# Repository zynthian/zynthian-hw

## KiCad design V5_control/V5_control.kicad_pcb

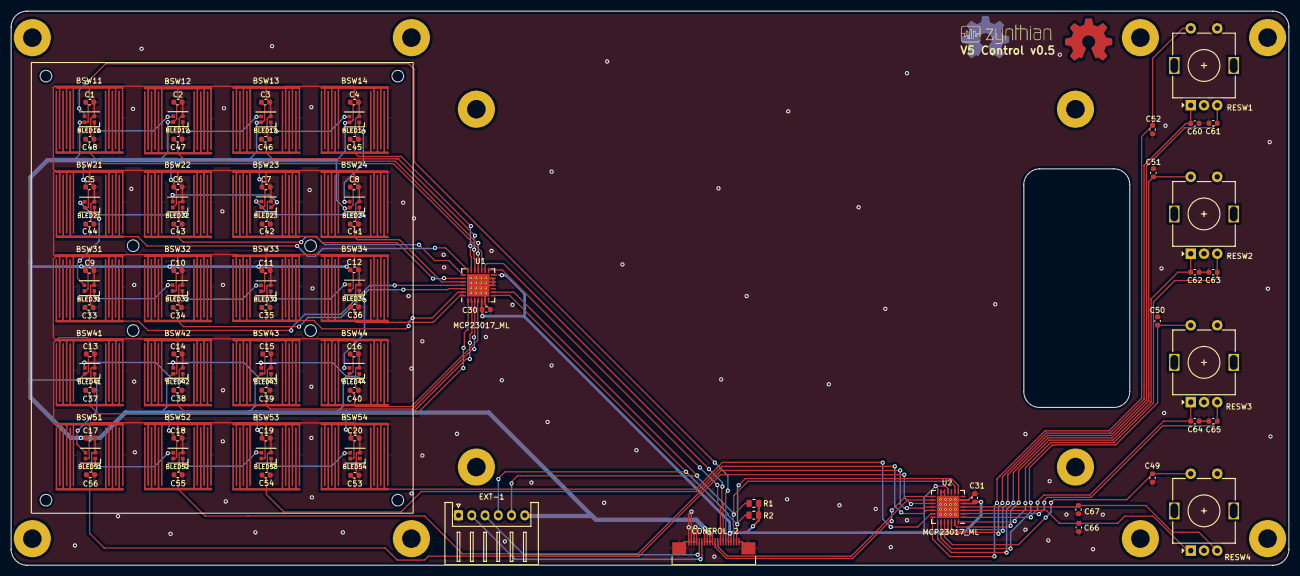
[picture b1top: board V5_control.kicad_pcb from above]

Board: 2 copper layers, 241.0 x 104.5 mm, 104 parts (0 on the bottom side), 63 nets.

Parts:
BLED11, BLED12, BLED13, BLED14, BLED21, BLED22, BLED23, BLED24, BLED31, BLED32, BLED33, BLED34, BLED41, BLED42, BLED43, BLED44, BLED51, BLED52, BLED53, BLED54: WS2812B; LED_WS2812-2020_2.2x2.0mm
BSW11, BSW12, BSW13, BSW14, BSW21, BSW22, BSW23, BSW24, BSW31, BSW32, BSW33, BSW34, BSW41, BSW42, BSW43, BSW44, BSW51, BSW52, BSW53, BSW54: SW_Push; V5-KeyPad_LED
C1, C2, C3, C4, C5, C6, C7, C8, C9, C10, C11, C12, C13, C14, C15, C16, C17, C18, C19, C20, C30, C31: 1uf; C_0603_1608Metric
C33, C34, C35, C36, C37, C38, C39, C40, C41, C42, C43, C44, C45, C46, C47, C48, C49, C50, C51, C52, C53, C54, C55, C56: 47nf16v; C_0603_1608Metric
C60, C61, C62, C63, C64, C65, C66, C67: 10nf16v; C_0603_1608Metric
CONTROL-2: Conn_01x22; SFV20R-4STE1LF_thinpads
EXT-1: Conn_01x06_Male; JST_XH_S6B-XH-A_1x06_P2.50mm_Horizontal
R1, R2: 10K; R_0805_2012Metric
RESW1, RESW2, RESW3, RESW4: Rotary_Encoder_Switch; RotaryEncoder_Alps_EC11E-Switch_Vertical_H20mm
U1, U2: MCP23017_ML; QFN-28-1EP_6x6mm_P0.65mm_EP4.25x4.25mm_ThermalVias

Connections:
3.3v: C30.1, C31.1, CONTROL-2.16, CONTROL-2.17, R1.1, R2.1, U1.5 (VDD), U1.14 (~RESET), U2.5 (VDD), U2.11 (A0), U2.14 (~RESET)
5v: BLED11.4 (VDD), BLED12.4 (VDD), BLED13.4 (VDD), BLED14.4 (VDD), BLED21.4 (VDD), BLED22.4 (VDD), BLED23.4 (VDD), BLED24.4 (VDD), BLED31.4 (VDD), BLED32.4 (VDD), BLED33.4 (VDD), BLED34.4 (VDD), BLED41.4 (VDD), BLED42.4 (VDD), BLED43.4 (VDD), BLED44.4 (VDD), BLED51.4 (VDD), BLED52.4 (VDD), BLED53.4 (VDD), BLED54.4 (VDD), C1.1, C2.1, C3.1, C4.1, C5.1, C6.1, C7.1, C8.1, C9.1, C10.1, C11.1, C12.1, C13.1, C14.1, C15.1, C16.1, C17.1, C18.1, C19.1, C20.1, CONTROL-2.7, CONTROL-2.8, CONTROL-2.9, CONTROL-2.10, EXT-1.6
GND: BLED11.2 (GND), BLED12.2 (GND), BLED13.2 (GND), BLED14.2 (GND), BLED21.2 (GND), BLED22.2 (GND), BLED23.2 (GND), BLED24.2 (GND), BLED31.2 (GND), BLED32.2 (GND), BLED33.2 (GND), BLED34.2 (GND), BLED41.2 (GND), BLED42.2 (GND), BLED43.2 (GND), BLED44.2 (GND), BLED51.2 (GND), BLED52.2 (GND), BLED53.2 (GND), BLED54.2 (GND), BSW11.2, BSW12.2, BSW13.2, BSW14.2, BSW21.2, BSW22.2, BSW23.2, BSW24.2, BSW31.2, BSW32.2, BSW33.2, BSW34.2, BSW41.2, BSW42.2, BSW43.2, BSW44.2, BSW51.2, BSW52.2, BSW53.2, BSW54.2, C1.2, C2.2, C3.2, C4.2, C5.2, C6.2, C7.2, C8.2, C9.2, C10.2, C11.2, C12.2, C13.2, C14.2, C15.2, C16.2, C17.2, C18.2, C19.2, C20.2, C30.2, C31.2, C33.1, C34.1, C35.1, C36.1, C37.1, C38.1, C39.1, C40.1, C41.2, C42.2, C43.2, C44.2, C45.2, C46.2, C47.2, C48.2, C49.2, C50.2, C51.2, C52.2, C53.2, C54.2, C55.2, C56.2, C60.1, C61.2, C62.1, C63.2, C64.1, C65.2, C66.1, C67.2, CONTROL-2.1, CONTROL-2.2, CONTROL-2.3, CONTROL-2.4, CONTROL-2.20, CONTROL-2.21, CONTROL-2.22, EXT-1.1, RESW1.C, RESW1.S2, RESW2.C, RESW2.S2, RESW3.C, RESW3.S2, RESW4.C, RESW4.S2, U1.6 (VSS), U1.11 (A0), U1.12 (A1), U1.13 (A2), U1.29 (EP), U2.6 (VSS), U2.12 (A1), U2.13 (A2), U2.29 (EP)
unnamed: BLED11.1 (DOUT), BLED12.3 (DIN)
unnamed: BLED11.3 (DIN), CONTROL-2.15
unnamed: BLED12.1 (DOUT), BLED13.3 (DIN)
unnamed: BLED13.1 (DOUT), BLED14.3 (DIN)
unnamed: BLED14.1 (DOUT), BLED24.3 (DIN)
unnamed: BLED21.1 (DOUT), BLED31.3 (DIN)
unnamed: BLED21.3 (DIN), BLED22.1 (DOUT)
unnamed: BLED22.3 (DIN), BLED23.1 (DOUT)
unnamed: BLED23.3 (DIN), BLED24.1 (DOUT)
unnamed: BLED31.1 (DOUT), BLED32.3 (DIN)
unnamed: BLED32.1 (DOUT), BLED33.3 (DIN)
unnamed: BLED33.1 (DOUT), BLED34.3 (DIN)
unnamed: BLED34.1 (DOUT), BLED44.3 (DIN)
unnamed: BLED41.1 (DOUT), BLED51.3 (DIN)
unnamed: BLED41.3 (DIN), BLED42.1 (DOUT)
unnamed: BLED42.3 (DIN), BLED43.1 (DOUT)
unnamed: BLED43.3 (DIN), BLED44.1 (DOUT)
unnamed: BLED51.1 (DOUT), BLED52.3 (DIN)
unnamed: BLED52.1 (DOUT), BLED53.3 (DIN)
unnamed: BLED53.1 (DOUT), BLED54.3 (DIN)
unnamed: BSW11.1, C48.1, U1.17 (GPA0)
unnamed: BSW12.1, C47.1, U1.18 (GPA1)
unnamed: BSW13.1, C46.1, U1.19 (GPA2)
unnamed: BSW14.1, C45.1, U1.20 (GPA3)
unnamed: BSW21.1, C44.1, U1.21 (GPA4)
unnamed: BSW22.1, C43.1, U1.22 (GPA5)
unnamed: BSW23.1, C42.1, U1.23 (GPA6)
unnamed: BSW24.1, C41.1, U1.24 (GPA7)
unnamed: BSW31.1, C33.2, U1.25 (GPB0)
unnamed: BSW32.1, C34.2, U1.26 (GPB1)
unnamed: BSW33.1, C35.2, U1.27 (GPB2)
unnamed: BSW34.1, C36.2, U1.28 (GPB3)
unnamed: BSW41.1, C37.2, U1.1 (GPB4)
unnamed: BSW42.1, C38.2, U1.2 (GPB5)
unnamed: BSW43.1, C39.2, U1.3 (GPB6)
unnamed: BSW44.1, C40.2, U1.4 (GPB7)
unnamed: BSW51.1, C56.1, U2.17 (GPA0)
unnamed: BSW52.1, C55.1, U2.18 (GPA1)
unnamed: BSW53.1, C54.1, U2.19 (GPA2)
unnamed: BSW54.1, C53.1, U2.20 (GPA3)
SCL: CONTROL-2.19, EXT-1.4, R2.2, U1.8 (SCK), U2.8 (SCK)
SDA: CONTROL-2.18, EXT-1.5, R1.2, U1.9 (SDA), U2.9 (SDA)
int1: CONTROL-2.14, U1.16 (INTA)
int2: CONTROL-2.13, U1.15 (INTB)
int3: CONTROL-2.12, U2.16 (INTA)
int4: CONTROL-2.11, U2.15 (INTB)
int6: CONTROL-2.5, EXT-1.3
int7: CONTROL-2.6, EXT-1.2
pot1_a: C60.2, RESW1.A, U2.25 (GPB0)
pot1_b: C61.1, RESW1.B, U2.26 (GPB1)
pot1_sw: C52.1, RESW1.S1, U2.21 (GPA4)
pot2_a: C62.2, RESW2.A, U2.27 (GPB2)
pot2_b: C63.1, RESW2.B, U2.28 (GPB3)
pot2_sw: C51.1, RESW2.S1, U2.22 (GPA5)
pot3_a: C64.2, RESW3.A, U2.1 (GPB4)
pot3_b: C65.1, RESW3.B, U2.2 (GPB5)
pot3_sw: C50.1, RESW3.S1, U2.23 (GPA6)
pot4_a: C66.2, RESW4.A, U2.3 (GPB6)
pot4_b: C67.1, RESW4.B, U2.4 (GPB7)
pot4_sw: C49.1, RESW4.S1, U2.24 (GPA7)

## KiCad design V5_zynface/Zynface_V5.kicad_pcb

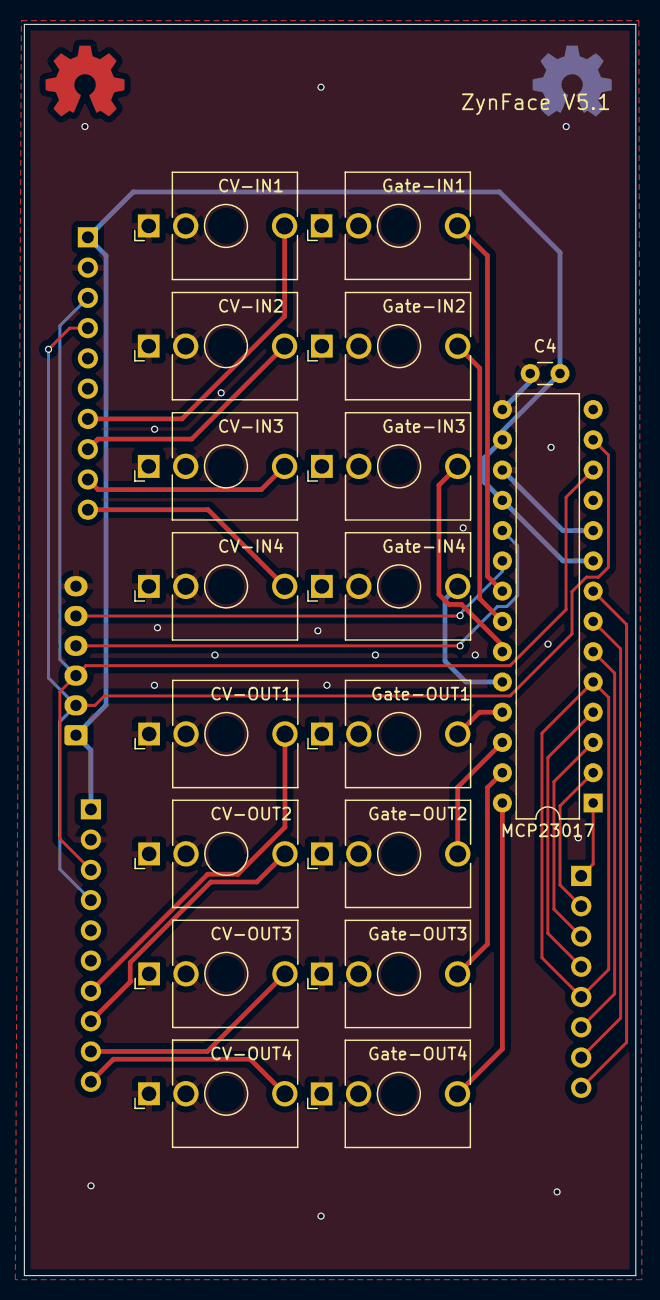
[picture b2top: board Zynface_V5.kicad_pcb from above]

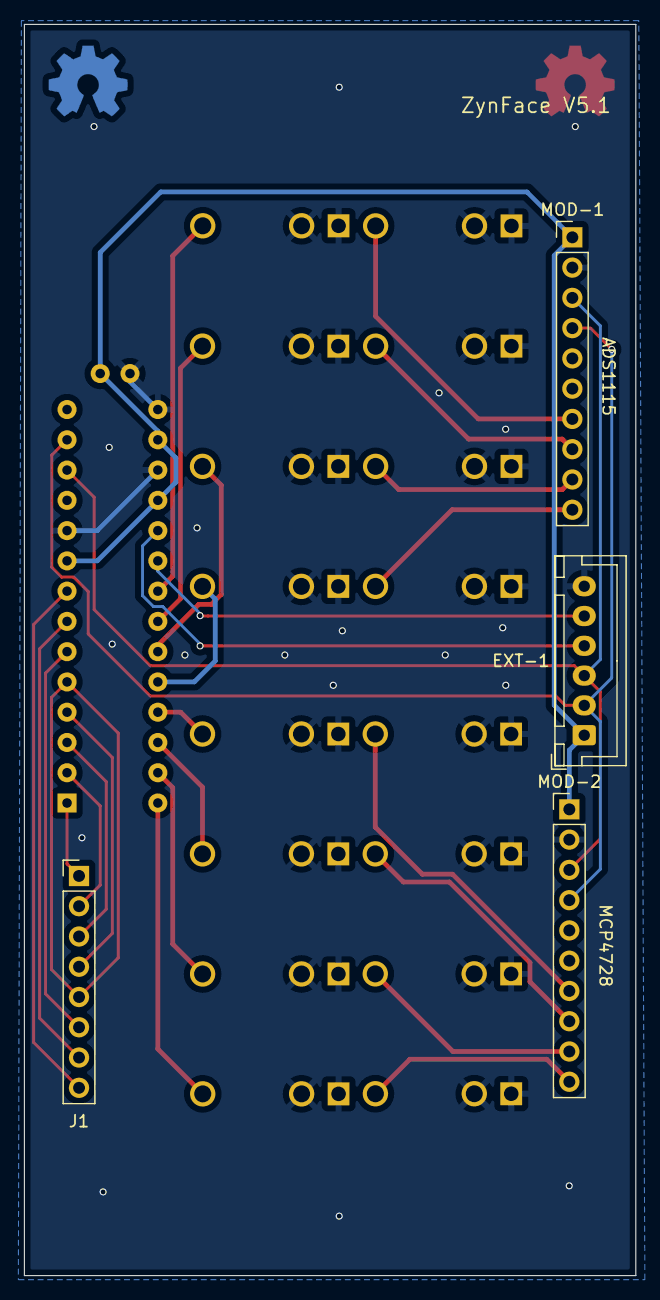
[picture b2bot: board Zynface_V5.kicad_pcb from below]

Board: 2 copper layers, 51.3 x 105.0 mm, 22 parts (4 on the bottom side), 30 nets.

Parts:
C4: 100n; C_Disc_D3.0mm_W1.6mm_P2.50mm
CV-IN1, CV-IN2, CV-IN3, CV-IN4: AudioJack2_SwitchT; Jack_3.5mm_QingPu_WQP-PJ398SM_Vertical_CircularHoles
CV-OUT1, CV-OUT2, CV-OUT3, CV-OUT4: AudioJack2_SwitchT; Jack_3.5mm_QingPu_WQP-PJ398SM_Vertical_CircularHoles
EXT-1: Conn_01x06_Male; JST_XH_B6B-XH-A_1x06_P2.50mm_Vertical
Gate-IN1, Gate-IN2, Gate-IN3, Gate-IN4: AudioJack2_SwitchT; Jack_3.5mm_QingPu_WQP-PJ398SM_Vertical_CircularHoles
Gate-OUT1, Gate-OUT2, Gate-OUT3, Gate-OUT4: AudioJack2_SwitchT; Jack_3.5mm_QingPu_WQP-PJ398SM_Vertical_CircularHoles
J1: Conn_01x08; PinHeader_1x08_P2.54mm_Vertical
MCP23017: MCP23017; DIP-28_W7.62mm
MOD-1: ADS1115; PinHeader_1x10_P2.54mm_Vertical
MOD-2: MCP4728; PinHeader_1x10_P2.54mm_Vertical

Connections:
+5V: C4.1, EXT-1.1, MCP23017.9 (VCC), MCP23017.16 (A1), MCP23017.18 (~RESET), MOD-1.1, MOD-2.1
CV-IN1: CV-IN1.T, MOD-1.7
CV-IN2: CV-IN2.T, MOD-1.8
CV-IN3: CV-IN3.T, MOD-1.9
CV-IN4: CV-IN4.T, MOD-1.10
CV-OUT1: CV-OUT1.T, MOD-2.7
CV-OUT2: CV-OUT2.T, MOD-2.8
CV-OUT3: CV-OUT3.T, MOD-2.9
CV-OUT4: CV-OUT4.T, MOD-2.10
GND: C4.2, CV-IN1.S, CV-IN1.TN, CV-IN2.S, CV-IN2.TN, CV-IN3.S, CV-IN3.TN, CV-IN4.S, CV-IN4.TN, CV-OUT1.S, CV-OUT1.TN, CV-OUT2.S, CV-OUT2.TN, CV-OUT3.S, CV-OUT3.TN, CV-OUT4.S, CV-OUT4.TN, EXT-1.6, Gate-IN1.S, Gate-IN1.TN, Gate-IN2.S, Gate-IN2.TN, Gate-IN3.S, Gate-IN3.TN, Gate-IN4.S, Gate-IN4.TN, Gate-OUT1.S, Gate-OUT1.TN, Gate-OUT2.S, Gate-OUT2.TN, Gate-OUT3.S, Gate-OUT3.TN, Gate-OUT4.S, Gate-OUT4.TN, MCP23017.10 (GND), MCP23017.15 (A0), MCP23017.17 (A2), MOD-1.2, MOD-2.2
GPB0: J1.1, MCP23017.1 (GPB0)
GPB1: J1.2, MCP23017.2 (GPB1)
GPB2: J1.3, MCP23017.3 (GPB2)
GPB3: J1.4, MCP23017.4 (GPB3)
GPB4: J1.5, MCP23017.5 (GPB4)
GPB5: J1.6, MCP23017.6 (GPB5)
GPB6: J1.7, MCP23017.7 (GPB6)
GPB7: J1.8, MCP23017.8 (GPB7)
Gate-IN1: Gate-IN1.T, MCP23017.21 (GPA0)
Gate-IN2: Gate-IN2.T, MCP23017.22 (GPA1)
Gate-IN3: Gate-IN3.T, MCP23017.23 (GPA2)
Gate-IN4: Gate-IN4.T, MCP23017.24 (GPA3)
Gate-OUT1: Gate-OUT1.T, MCP23017.25 (GPA4)
Gate-OUT2: Gate-OUT2.T, MCP23017.26 (GPA5)
Gate-OUT3: Gate-OUT3.T, MCP23017.27 (GPA6)
Gate-OUT4: Gate-OUT4.T, MCP23017.28 (GPA7)
INTA: EXT-1.5, MCP23017.20 (INTA)
INTB: EXT-1.4, MCP23017.19 (INTB)
SCL: EXT-1.3, MCP23017.12 (SCL), MOD-1.3, MOD-2.3
SDA: EXT-1.2, MCP23017.13 (SDA), MOD-1.4, MOD-2.4

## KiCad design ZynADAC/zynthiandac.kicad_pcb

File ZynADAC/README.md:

# ZynADAC

ZynADAC is an Input/Output Audio Interface for the RBPi.

It features:

+ Burr Brown (Texas Instruments) PCM5242 (DAC)
+ Burr Brown (Texas Instruments) PCM1863 (ADC)
+ 2 x ultra-low jitter oscillators (44.1 & 48 KHz)
+ 3 x dedicated ultra-low noise LDOs (analog DAC, analog ADC, digital)

This design is inspired in the [Hifiberry](https://hifiberry.com) soundcards.

[](
http://creativecommons.org/licenses/by-sa/4.0/)
This work is licensed under a [Creative Commons Attribution-ShareAlike 4.0 International License](http://creativecommons.org/licenses/by-sa/4.0/)

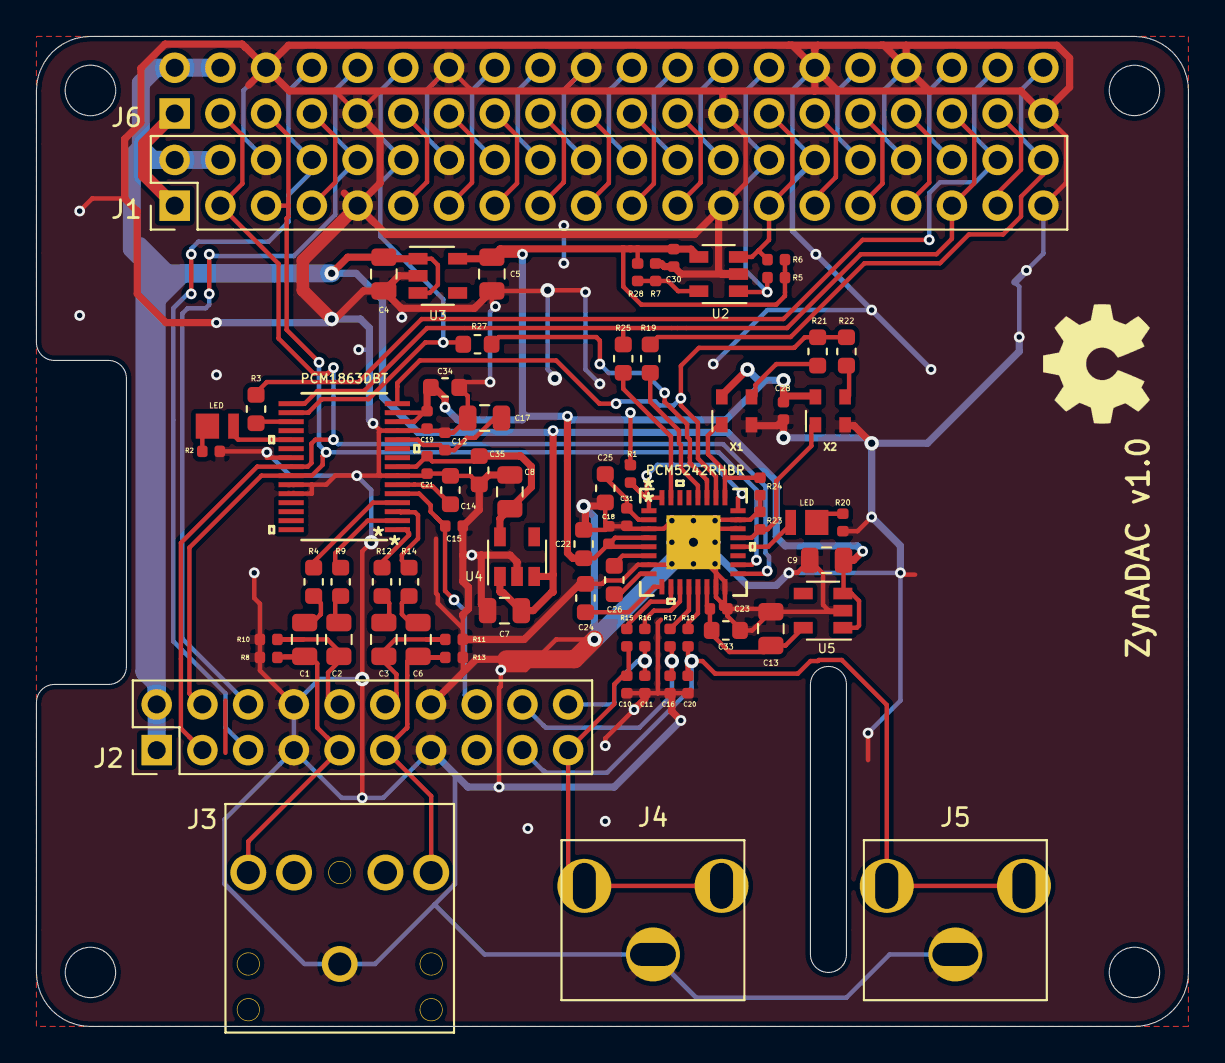
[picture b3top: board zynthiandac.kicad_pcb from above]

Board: 2 copper layers, 64.0 x 55.0 mm, 75 parts (1 on the bottom side), 77 nets.

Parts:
C1, C2, C3, C4, C5, C6, C7, C8, C9, C13, C17: 10uf16v; C_0805_2012Metric
C10, C11, C16, C20: 2,2nf50v; C_0402_1005Metric
C12, C21, C28, C30, C31: 100nf25v; C_0402_1005Metric
C14, C25, C33, C34, C35: 1uf16v; C_0603_1608Metric
C15: 100nf25V; C_0402_1005Metric
C18: 100nF25V; C_0402_1005Metric
C19, C23: 100nf16v; C_0402_1005Metric
C22: 1uf16V; C_0603_1608Metric
C24, C26: 1uf 16v; C_0603_1608Metric
D1, D2: LED; led_0806
J1: Conn_2x20; PinHeader_2x20_P2.54mm_Vertical
J2: Conn_02x10_Odd_Even; PinHeader_2x10_P2.54mm_Vertical
J3: AudioJack2_Ground_Switch; conn_audio5
J4, J5: AudioJack2_Ground; conn_audio3
J6: Conn_2x20; PinSocket_2x20_P2.54mm_Vertical
R1, R2, R20, R23, R24: 10k; R_0402_1005Metric
R3, R4, R9, R12, R14, R19, R21, R22, R25, R27: 100R; R_0603_1608Metric
R5, R6, R7, R28: 3K8; R_0402_1005Metric
R8, R10, R11, R13: 100K; R_0402_1005Metric
R15, R16, R17, R18: 470R; R_0402_1005Metric
U1: PCM1863DBT
U2: AT24CS01-STUM; SOT-23-5
U3, U4, U5: ncp163; SOT-23-5
U6: PCM5242RHBR
X1: 22.5792Mhz; Oscillator_SMD_Abracon_ASDMB-4Pin_2.5x2.0mm
X2: 24.576Mhz; Oscillator_SMD_Abracon_ASDMB-4Pin_2.5x2.0mm

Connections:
5v: C4.1, C7.1, C9.1, J1.2, J1.4, J2.1, J2.2, J6.2, J6.4, U3.1, U3.3, U4.1, U4.3, U5.1, U5.3
AVDD: C13.1, C23.1, C33.2, U5.5, U6.14
AVDD2: C8.1, C21.1, C35.1, U1.8, U4.5
DIN: R19.1, U6.28
DVDD: C5.1, C18.2, C19.1, C22.2, C28.1, C30.2, C34.1, R1.2, R5.2, R6.2, R28.1, U1.13, U1.14, U2.4, U3.5, U6.4, U6.5, X1.4, X2.4
GND: C4.2, C5.2, C7.2, C8.2, C9.2, C10.2, C11.2, C12.2, C13.2, C14.1, C15.1, C16.2, C17.2, C18.1, C19.2, C20.2, C21.2, C22.1, C23.2, C24.1, C25.1, C28.2, C30.1, C31.1, C33.1, C34.2, C35.2, J1.6, J1.9, J1.14, J1.20, J1.25, J1.30, J1.34, J1.39, J2.7, J2.8, J2.13, J2.14, J3.G, J4.G, J5.G, J6.6, J6.9, J6.14, J6.20, J6.25, J6.30, J6.34, J6.39, R2.1, R7.2, R8.1, R10.1, R11.1, R13.1, R20.1, R23.2, R24.2, U1.7, U1.12, U1.22, U1.25, U1.26, U2.2, U3.2, U4.2, U5.2, U6.3, U6.7, U6.15, U6.16, U6.22, U6.23, U6.33, X1.2, X2.2
ID_SC: J1.28, J6.28, R5.1, U2.1
ID_SD: J1.27, J6.27, R6.1, U2.3
unnamed: C1.1, R4.2
unnamed: C2.1, R9.2
unnamed: C3.1, R12.2
unnamed: C6.1, R14.2
unnamed: C12.1, C17.1, U1.11
unnamed: C14.2, U1.6
unnamed: C24.2, U6.9
unnamed: C25.2, C31.2, U6.2
unnamed: C26.1, U6.8
unnamed: C26.2, U6.6
unnamed: D1.1, R2.2
unnamed: D1.2, U1.20
unnamed: D2.1, R20.2
unnamed: D2.2, U6.20
unnamed: J1.1, J6.1
unnamed: J1.7, J6.7
unnamed: J1.11, J6.11
unnamed: J1.12, J6.12, R27.1, U1.17
unnamed: J1.13, J6.13
unnamed: J1.15, J6.15
unnamed: J1.16, J6.16
unnamed: J1.17, J6.17
unnamed: J1.18, J6.18
unnamed: J1.19, J6.19
unnamed: J1.21, J6.21
unnamed: J1.22, J6.22
unnamed: J1.23, J6.23
unnamed: J1.24, J6.24
unnamed: J1.26, J6.26
unnamed: J1.29, J6.29
unnamed: J1.31, J6.31
unnamed: J1.32, J6.32
unnamed: J1.33, J6.33
unnamed: J1.35, J6.35, R25.1, U1.16
unnamed: J1.36, J6.36
unnamed: J1.37, J6.37
unnamed: J1.38, J6.38, R3.2
unnamed: J1.40, J6.40, R19.2
unnamed: R1.1, U6.1, U6.24, U6.32
unnamed: R3.1, U1.18
unnamed: R4.1, U1.4
unnamed: R9.1, U1.2
unnamed: R12.1, U1.1
unnamed: R14.1, U1.3
unnamed: R15.1, U6.10
unnamed: R16.1, U6.11
unnamed: R17.1, U6.12
unnamed: R18.1, U6.13
unnamed: R21.1, X1.3
unnamed: R21.2, R22.2, U1.15, U6.26
unnamed: R22.1, X2.3
unnamed: R23.1, U6.21, X2.1
unnamed: R24.1, U6.25, X1.1
unnamed: R25.2, U6.31
unnamed: R27.2, U6.27
unnamed: R7.1, R28.2, U2.5
gpio14: J1.8, J2.5, J6.8
gpio15: J1.10, J2.6, J6.10
inl+: C6.2, J2.11, J3.TN, R13.2
inl-: C3.2, J2.12, R11.2
inr+: C1.2, J2.9, J3.S, R8.2
inr-: C2.2, J2.10, R10.2
micbias: C15.2, J2.16, U1.5
outl+: C10.1, J2.19, J4.S, J4.T, R15.2
outl-: C11.1, J2.20, R16.2
outr+: C20.1, J2.17, J5.S, J5.T, R18.2
outr-: C16.1, J2.18, R17.2
scl: J1.5, J2.4, J6.5, U1.24, U6.18
sda: J1.3, J2.3, J6.3, U1.23, U6.17

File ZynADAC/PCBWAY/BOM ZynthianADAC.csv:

Ref. PCB,Ref. Manufacturer,Description,Quantity,Price 1000,Subtotal,URL
U1,PCM1863DBTR,"ADC, 30-TSSOP",1,"1,984","1,984",https://www.digikey.es/product-detail/es/texas-instruments/P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
U2,AT24C32E-STUM-T,"EEPROM, SOT-23-5 ",1,"0,2","0,2",https://www.digikey.es/product-detail/es/microchip-technolog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
"U3,U4,U5",NCP163ASN330T1G,"LDO 3.3v Ultra Low Noise, SOT-23-5 ",3,"0,12","0,36",https://www.digikey.es/product-detail/es/on-semiconductor/NC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
U6,PCM5242RHBR,"DAC, 32-VQFN",1,"3,071","3,071",https://www.digikey.es/product-detail/es/texas-instruments/P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
"C1,C2,C3,C4,C5,C6,C7,C8,C9,C13,C17",CL21A106KOQNNNE,10µF ±10% 16V Ceramic Capacitor X5R 0805 (2012),11,"0,022","0,242",https://www.digikey.es/product-detail/es/samsung-electro-mec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
"C14,C22,C24,C26,C33,C34,C35",CL10A105KA8NNNC,1µF ±10% 25V Ceramic Capacitor X5R 0603 (1608),7,"0,00742","0,05194",https://www.digikey.es/product-detail/es/samsung-electro-mec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
"C12,C15,C18,C19,C21,C23,C28,C30,C31",CL05A104KA5NNNC,0.1µF ±10% 25V Ceramic Capacitor X5R 0402 (1005),9,"0,0022","0,0198",https://www.digikey.es/product-detail/es/samsung-electro-mec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
"C10,C11,C16,C20",CC0402KRX7R9BB222,2200pF ±10% 50V Ceramic Capacitor X7R 0402 (1005),4,"0,004","0,016",https://www.digikey.es/product-detail/es/yageo/CC0402KRX7R9B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
X1,SIT8008BC-21-33E-22.579200E,"XO Oscillator 22.5792Mhz Low Power, 4-SMD",1,"0,64","0,64",https://www.digikey.es/product-detail/es/sitime/SIT8008BC-21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
X2,SIT1602BI-21-33E-24.576000D,"XO Oscillator 24.576Mhz Low Power, 4-SMD",1,"0,64","0,64",https://www.digikey.es/product-detail/es/sitime/SIT1602BI-21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
"D1,D2",MP-2016-1100-27-80,LED Low Power 0806 (2016) ,2,"0,022","0,044",https://www.digikey.es/product-detail/es/luminus-devices-inc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
"R8,R10,R11,R13",CR0402-FX-1003GLF,100K ±1% 1/16W Resistor 0402 (1005),4,"0,001","0,004",https://www.digikey.es/product-detail/es/bourns-inc/CR0402-F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
"R23,R24,R1,R2,R20",RMCF0402JT10K0,10K ±5% 1/16W Resistor 0402 (1005),5,"0,0014","0,007",https://www.digikey.es/product-detail/es/stackpole-electroni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
"R5,R6",RMCF0402JT3K90,3K9 ±5% 1/16W Resistor 0402 (1005),2,"0,0011","0,0022",https://www.digikey.es/product-detail/es/stackpole-electroni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
"R15,R16,R17,R18",RMCF0402FT470R,470 Ohm 1% 1/16W Resistor 0402 (1005),4,"0,0015","0,006",https://www.digikey.es/product-detail/es/stackpole-electroni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
"R4,R9,R12,R14,R3,R21,R22,R25,R27,R19",RMCF0603FT100R,100 Ohm 1% 1/10W Resistor 0603 (1608),11,"0,002","0,022",https://www.digikey.es/product-detail/es/stackpole-electroni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
J1,,"PinHeader 2x20 pin, 2.54mm (Male)",,,,
J6,,"PinSocket 2x20 pin, 2.54mm (Female)",,,,
J2,,"PinHeader 2x10 pin, 2.54mm (Male)",,,,
"J9,J3,J4,J5",NOT MOUNT!,,,,,
,,,,,,
,,,,TOTAL:,"7,30994",

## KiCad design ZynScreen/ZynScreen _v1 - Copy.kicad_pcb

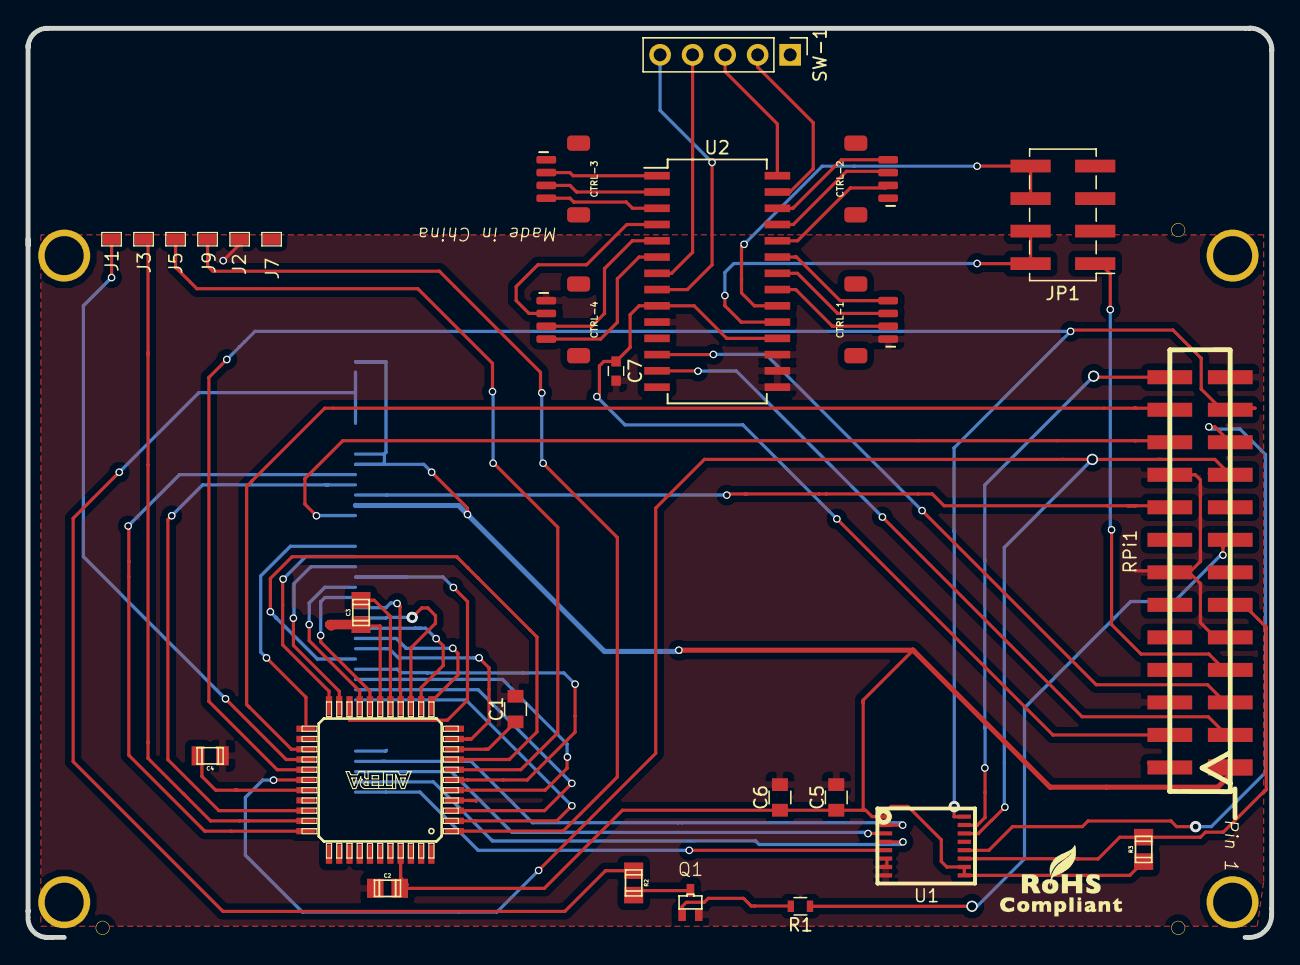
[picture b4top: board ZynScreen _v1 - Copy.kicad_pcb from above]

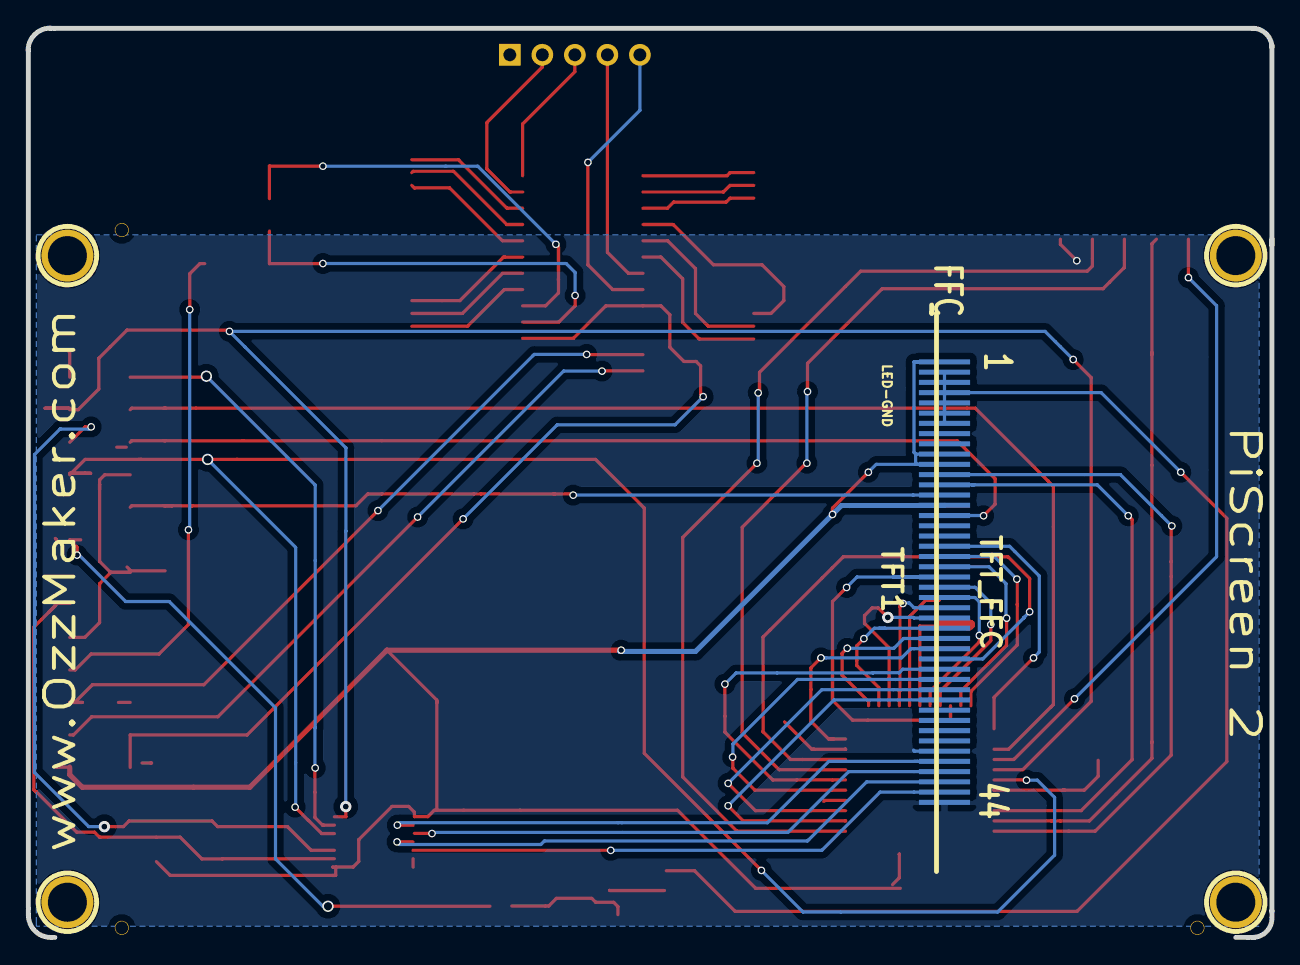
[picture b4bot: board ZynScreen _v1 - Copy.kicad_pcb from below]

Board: 2 copper layers, 97.1 x 71.0 mm, 38 parts (5 on the bottom side), 63 nets.

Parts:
1mm_tft-1, 1mm_tft-2, 1mm_tft-3: P***; 1pin
C1, C5, C6: 100nF; C_0805
C2, C3, C4: 100nF; c_0805
C7: 100nF; C_0603
CTRL-1: CTRL1; BM04B-SRSS-TB
CTRL-2: CTRL2; BM04B-SRSS-TB
CTRL-3: CTRL3; BM04B-SRSS-TB
CTRL-4: CTRL4; BM04B-SRSS-TB
G2: LOGO3; LOzzMaker-Skull-copper
G3: LOGO2; LOzzMaker-Skull-copper-solder-mask
G222: LOGO; Logo_copper_ROHS_10x5.6mm
IC1: EPM3032A; altera-TQFP44
J1, J2, J3, J5, J7, J9: Conn_01x01; JTAG-1PAD
JP1: Conn_02x04_Odd_Even; Pin_Header_Straight_2x04_Pitch2.54mm_SMD
Mount1, Mount2, Mount3, Mount4: P***; 1pin
Q1: Q_NPN_BEC; SOT323
R1: 1K; R_0603
R2: 4.7; c_0805
R3: 100K; c_0805
RPi1: RASPBERRY_IO; header-SMD-26pin
SW-1: Conn_01x05; Pin_Header_Straight_1x05_Pitch2.54mm
TFT1: TFT_FFC; FFC_TFT
U1: XPT2046; TSSOP-16
U2: MCP23017; SOIC-28W_7.5x18.7mm_Pitch1.27mm

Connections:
+3V3: C1.1, C2.1, C3.1, C4.1, C5.1, C6.1, IC1.9, IC1.17, IC1.29, IC1.41, J7.1, R3.2, RPi1.1, TFT1.1, TFT1.10, TFT1.11, TFT1.15, U1.1, U1.9, U1.10
+5V: C7.1, RPi1.2, RPi1.4, U2.9, U2.18
/BACKLIGHT: R1.1, RPi1.15
/CE0: IC1.25, RPi1.24
/CE1: RPi1.26, U1.15
/CLK: IC1.27, RPi1.23, U1.16
/DB00: IC1.2, TFT1.34
/DB01: IC1.3, TFT1.33
/DB02: IC1.5, TFT1.32
/DB03: IC1.6, TFT1.31
/DB04: IC1.8, TFT1.30
/DB05: IC1.10, TFT1.29
/DB06: IC1.12, TFT1.28
/DB07: IC1.13, TFT1.27
/DB08: IC1.14, TFT1.26
/DB09: IC1.15, TFT1.25
/DB10: IC1.18, TFT1.24
/DB11: IC1.19, TFT1.23
/DB12: IC1.20, TFT1.22
/DB13: IC1.21, TFT1.21
/DB14: IC1.22, TFT1.20
/DB15: IC1.23, TFT1.19
/MISO: RPi1.21, U1.12
/MOSI: IC1.28, RPi1.19, U1.14
/RESET: RPi1.22, TFT1.16
/RS: RPi1.18, TFT1.14
/SCL: RPi1.5, U2.12
/SDA: RPi1.3, U2.13
/TCK: IC1.26, J1.1
/TDI: IC1.1, J9.1
/TDO: IC1.32, J3.1
/TMS: IC1.7, J5.1
/XL: TFT1.40, U1.2
/XR: TFT1.42, U1.4
/YD: TFT1.41, U1.3
/YU: TFT1.43, U1.5
GND: C1.2, C2.2, C3.2, C4.2, C5.2, C6.2, C7.2, CTRL-1.1, CTRL-2.1, CTRL-3.1, CTRL-4.1, IC1.4, IC1.11, IC1.16, IC1.24, IC1.30, IC1.36, J2.1, Q1.2, RPi1.6, RPi1.9, RPi1.14, RPi1.20, RPi1.25, SW-1.1, TFT1.8, TFT1.39, TFT1.44, U1.6, U1.7, U1.8, U2.10, U2.15, U2.16, U2.17
INTA: JP1.6, JP1.8, U2.20
INTA-1: JP1.5, R3.1, RPi1.11, U1.11
INTA-2: JP1.3, JP1.7, RPi1.12
INTB: JP1.2, JP1.4, U2.19
INTB-1: JP1.1, RPi1.7
unnamed: CTRL-1.2, U2.21
unnamed: CTRL-1.3, U2.22
unnamed: CTRL-1.4, U2.23
unnamed: CTRL-2.2, U2.24
unnamed: CTRL-2.3, U2.25
unnamed: CTRL-2.4, U2.26
unnamed: CTRL-3.2, U2.1
unnamed: CTRL-3.3, U2.2
unnamed: CTRL-3.4, U2.3
unnamed: CTRL-4.2, U2.4
unnamed: CTRL-4.3, U2.5
unnamed: CTRL-4.4, U2.6
unnamed: IC1.31, TFT1.13
unnamed: IC1.33, TFT1.12
unnamed: Q1.1, R1.2
unnamed: Q1.3, R2.1
unnamed: R2.2, TFT1.2, TFT1.3, TFT1.4, TFT1.5, TFT1.6, TFT1.7
unnamed: SW-1.2, U2.27
unnamed: SW-1.3, U2.28
unnamed: SW-1.4, U2.7
unnamed: SW-1.5, U2.8

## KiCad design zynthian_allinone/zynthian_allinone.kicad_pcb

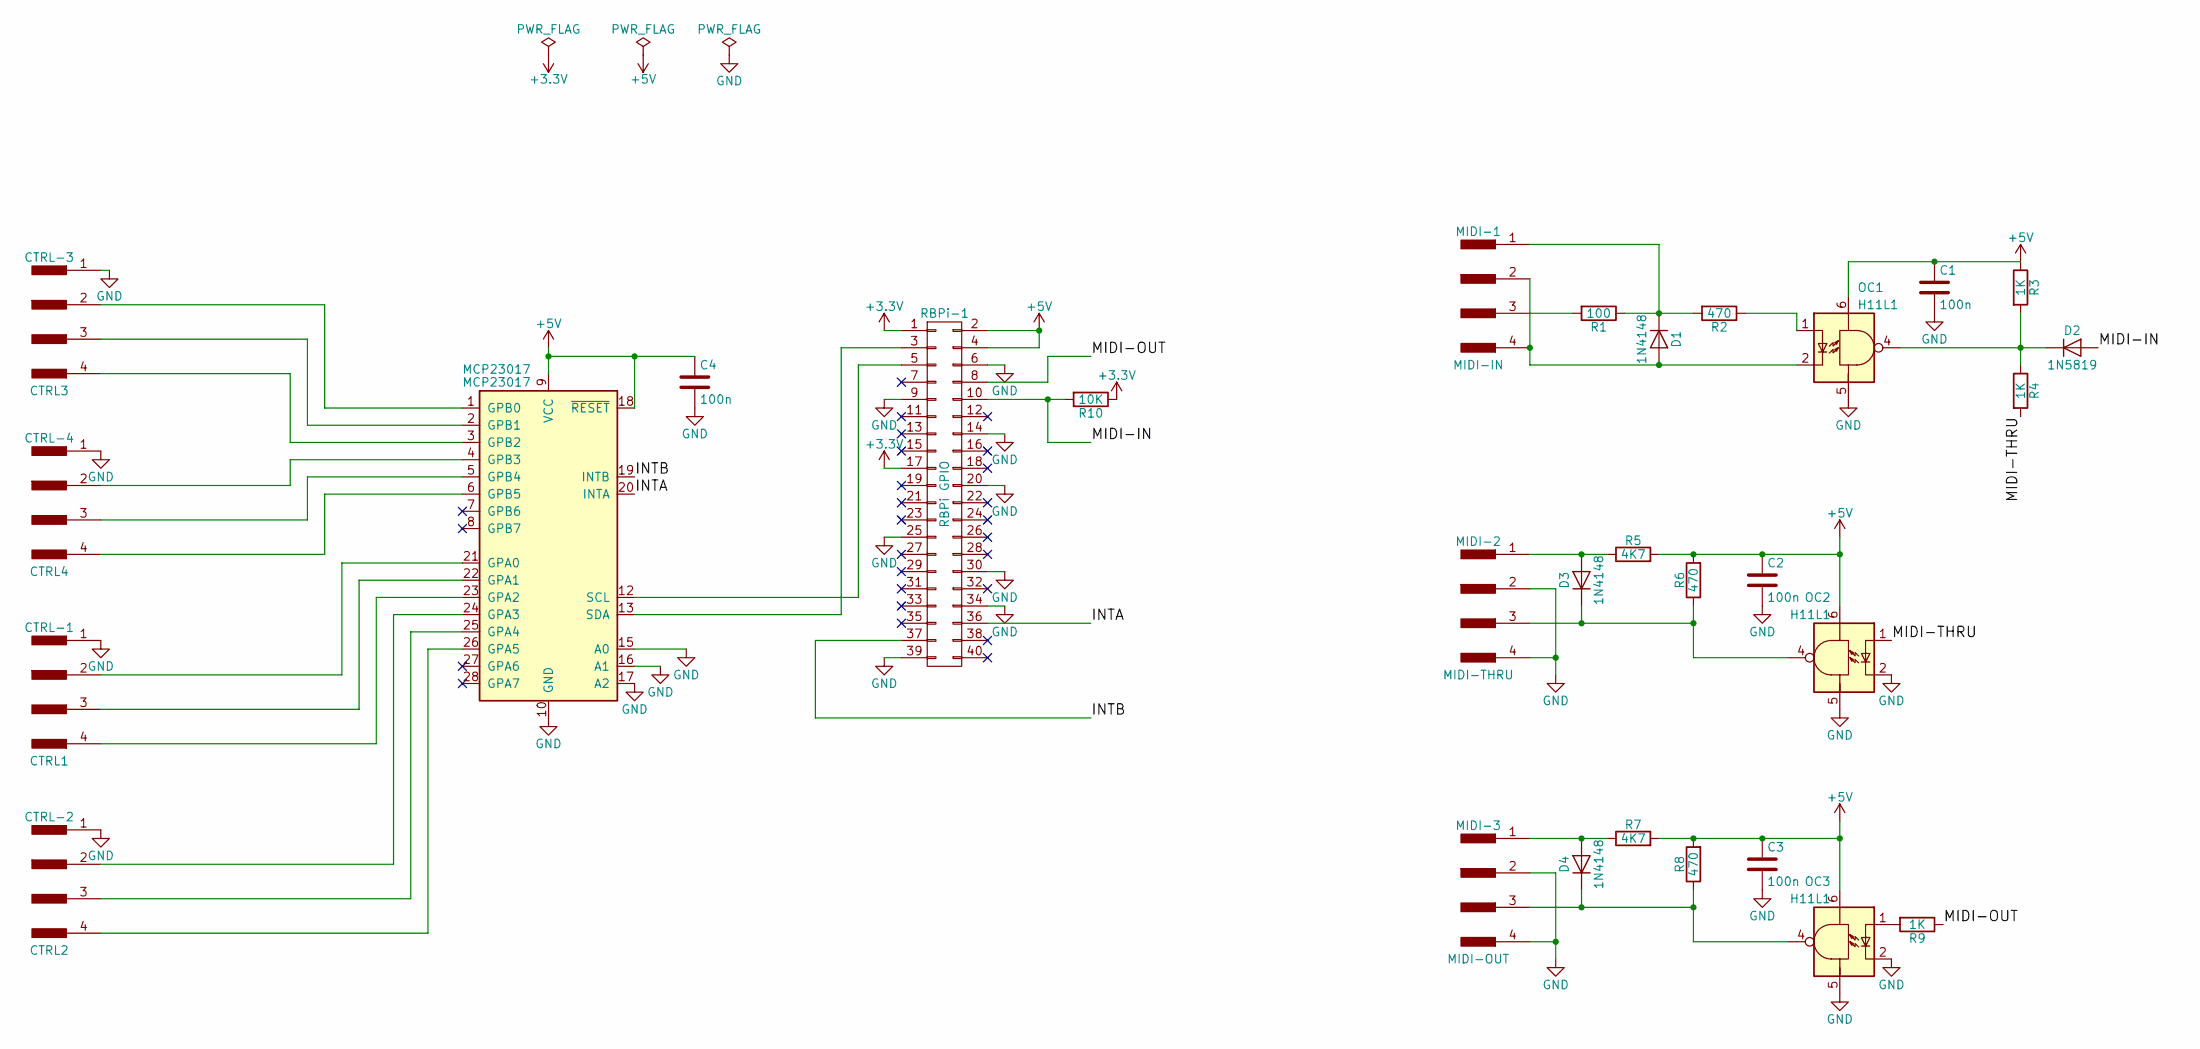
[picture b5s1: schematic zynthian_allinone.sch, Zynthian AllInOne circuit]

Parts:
C1, C2, C3, C4: 100n; C_Disc_D3.0mm_W1.6mm_P2.50mm
CTRL-1: CTRL1; JST_XH_B04B-XH-A_04x2.50mm_Straight
CTRL-2: CTRL2; JST_XH_B04B-XH-A_04x2.50mm_Straight
CTRL-3: CTRL3; JST_XH_B04B-XH-A_04x2.50mm_Straight
CTRL-4: CTRL4; JST_XH_B04B-XH-A_04x2.50mm_Straight
D1, D3, D4: 1N4148; D3
D2: 1N5819; D3
MCP23017: MCP23017; DIP-28_W7.62mm
MIDI-1: MIDI-IN; JST_XH_B04B-XH-A_04x2.50mm_Straight
MIDI-2: MIDI-THRU; JST_XH_B04B-XH-A_04x2.50mm_Straight
MIDI-3: MIDI-OUT; JST_XH_B04B-XH-A_04x2.50mm_Straight
OC1, OC2, OC3: H11L1; DIP-6_W7.62mm
R1: 100; R4
R2, R6, R8: 470; R4
R3, R4, R9: 1K; R4
R5, R7: 4K7; R4
R10: 10K; R4
RBPi-1: RBPi GPIO; Pin_Header_Straight_2x20_Pitch2.54mm

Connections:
+3V3: R10.1, RBPi-1.1, RBPi-1.17
+5V: C1.1, C2.1, C3.1, C4.1, MCP23017.9 (VCC), MCP23017.18 (~RESET), OC1.6, OC2.6, OC3.6, R3.1, R5.2, R6.2, R7.2, R8.2, RBPi-1.2, RBPi-1.4
/INTA: MCP23017.20 (INTA), RBPi-1.36
/INTB: MCP23017.19 (INTB), RBPi-1.37
/MIDI-IN: D2.2 (A), R10.2, RBPi-1.10
/MIDI-OUT: R9.1, RBPi-1.8
/MIDI-THRU: OC2.1, R4.2
GND: C1.2, C2.2, C3.2, C4.2, CTRL-1.1, CTRL-2.1, CTRL-3.1, CTRL-4.1, MCP23017.10 (GND), MCP23017.15 (A0), MCP23017.16 (A1), MCP23017.17 (A2), MIDI-2.2, MIDI-2.4, MIDI-3.2, MIDI-3.4, OC1.5, OC2.2, OC2.5, OC3.2, OC3.5, RBPi-1.6, RBPi-1.9, RBPi-1.14, RBPi-1.20, RBPi-1.25, RBPi-1.30, RBPi-1.34, RBPi-1.39
unnamed: CTRL-1.2, MCP23017.21 (GPA0)
unnamed: CTRL-1.3, MCP23017.22 (GPA1)
unnamed: CTRL-1.4, MCP23017.23 (GPA2)
unnamed: CTRL-2.2, MCP23017.24 (GPA3)
unnamed: CTRL-2.3, MCP23017.25 (GPA4)
unnamed: CTRL-2.4, MCP23017.26 (GPA5)
unnamed: CTRL-3.2, MCP23017.1 (GPB0)
unnamed: CTRL-3.3, MCP23017.2 (GPB1)
unnamed: CTRL-3.4, MCP23017.3 (GPB2)
unnamed: CTRL-4.2, MCP23017.4 (GPB3)
unnamed: CTRL-4.3, MCP23017.5 (GPB4)
unnamed: CTRL-4.4, MCP23017.6 (GPB5)
unnamed: D1.1 (K), MIDI-1.1, R1.1, R2.2
unnamed: D1.2 (A), MIDI-1.2, MIDI-1.4, OC1.2
unnamed: D2.1 (K), OC1.4, R3.2, R4.1
unnamed: D3.1 (K), MIDI-2.3, OC2.4, R6.1
unnamed: D3.2 (A), MIDI-2.1, R5.1
unnamed: D4.1 (K), MIDI-3.3, OC3.4, R8.1
unnamed: D4.2 (A), MIDI-3.1, R7.1
unnamed: MCP23017.12 (SCL), RBPi-1.5
unnamed: MCP23017.13 (SDA), RBPi-1.3
unnamed: MIDI-1.3, R1.2
unnamed: OC1.1, R2.1
unnamed: OC3.1, R9.2

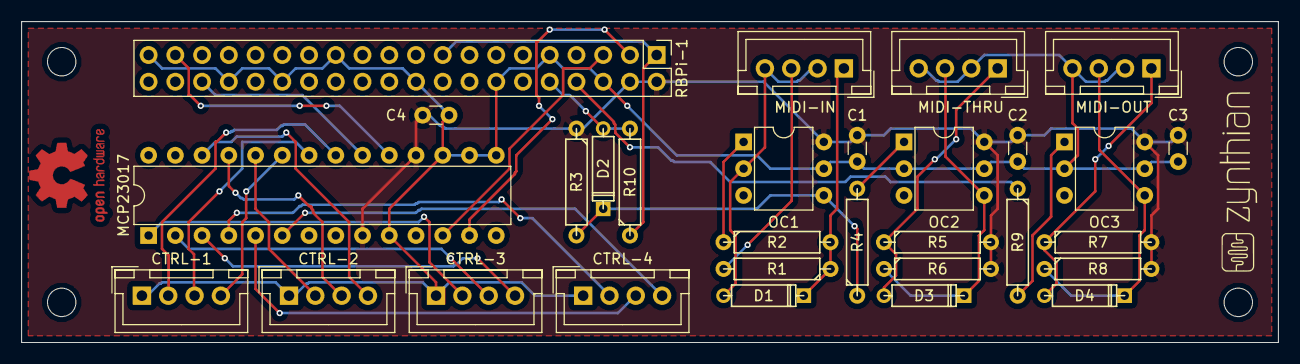
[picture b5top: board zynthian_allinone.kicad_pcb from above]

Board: 2 copper layers, 119.4 x 30.5 mm, 34 parts (0 on the bottom side), 32 nets.

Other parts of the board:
MH1, MH2, MH3, MH4: MountingHole_2.7mm_M2.5_DIN965

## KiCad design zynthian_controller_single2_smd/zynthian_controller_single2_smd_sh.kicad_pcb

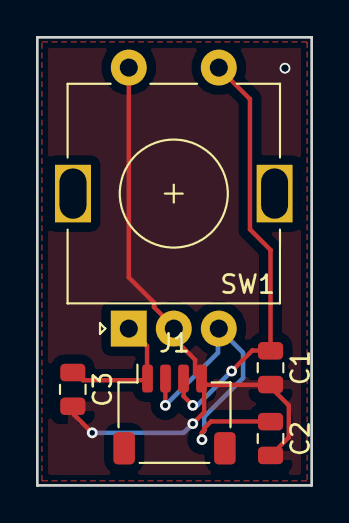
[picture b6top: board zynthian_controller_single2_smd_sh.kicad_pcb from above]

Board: 2 copper layers, 15.2 x 24.9 mm, 5 parts (0 on the bottom side), 4 nets.

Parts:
C1: 100nF; C_0805_2012Metric
C2, C3: 10nF; C_0805_2012Metric
J1: CONN_01X04; JST_SH_SM04B-SRSS-TB_1x04-1MP_P1.00mm_Horizontal
SW1: Rotary_Encoder_Switch; RotaryEncoder_Alps_EC11E-Switch_Vertical_H20mm

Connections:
CON-1: C3.1, J1.1
CON-2: C2.1, J1.2
CON-3: C1.1, J1.3
CON-4: C1.2, C2.2, C3.2, J1.4

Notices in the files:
parts and their libraries:
Copyright 2021 Accelerated Designs. All rights reserved.
Copyright 2016 Accelerated Designs. All rights reserved.
